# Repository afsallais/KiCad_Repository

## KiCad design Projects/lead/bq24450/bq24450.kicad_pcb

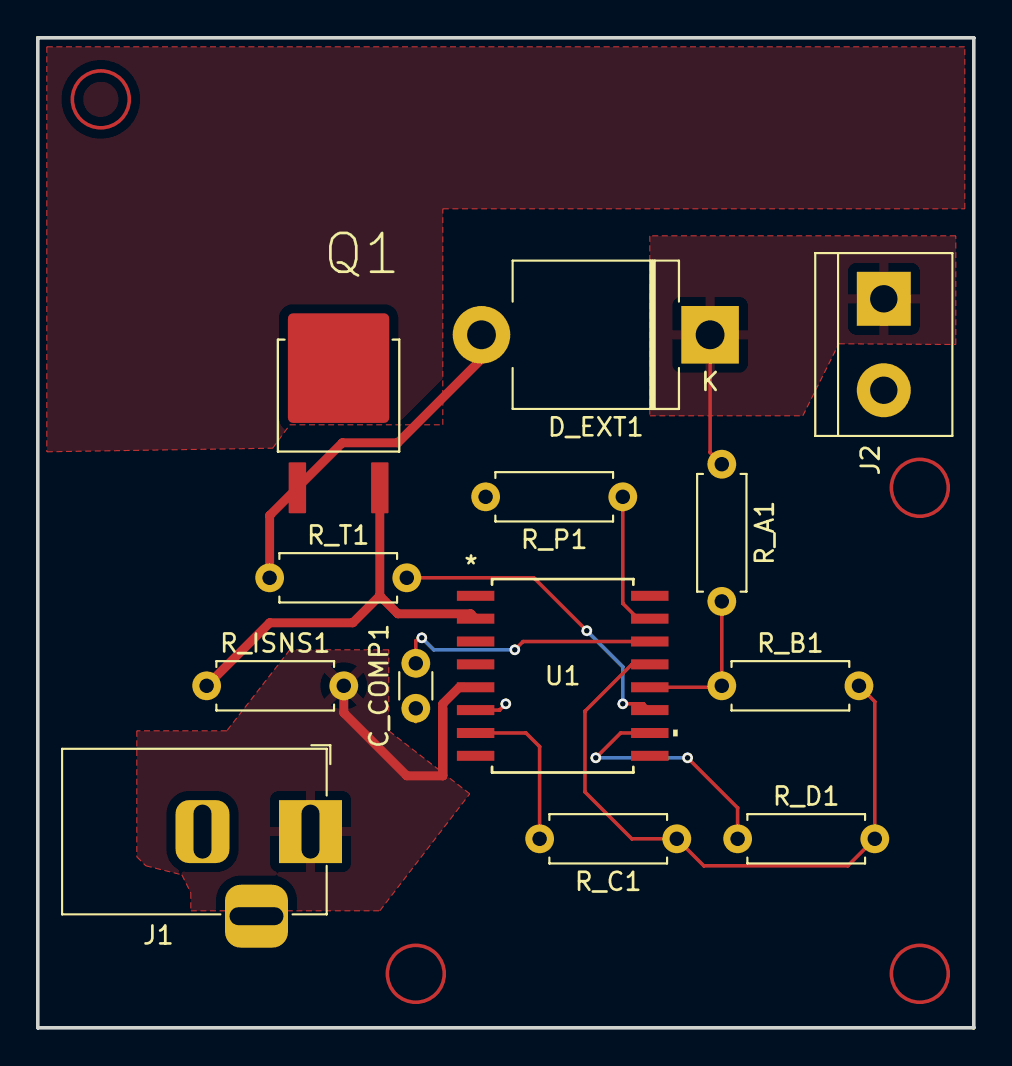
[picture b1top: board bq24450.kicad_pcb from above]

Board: 2 copper layers, 52.0 x 55.0 mm, 13 parts (0 on the bottom side), 13 nets.

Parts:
C_COMP1: C; C_Disc_D3.0mm_W1.6mm_P2.50mm
D_EXT1: D; D_5KPW_P12.70mm_Horizontal
J1: Jack-DC; BarrelJack_Horizontal
J2: Screw_Terminal_01x02; TerminalBlock_bornier-2_P5.08mm
Q1: PNP; MJD127T4GMJD127T4G
R_A1: R; R_Axial_DIN0207_L6.3mm_D2.5mm_P7.62mm_Horizontal
R_B1: R; R_Axial_DIN0207_L6.3mm_D2.5mm_P7.62mm_Horizontal
R_C1: R; R_Axial_DIN0207_L6.3mm_D2.5mm_P7.62mm_Horizontal
R_D1: R; R_Axial_DIN0207_L6.3mm_D2.5mm_P7.62mm_Horizontal
R_ISNS1: R; R_Axial_DIN0207_L6.3mm_D2.5mm_P7.62mm_Horizontal
R_P1: R; R_Axial_DIN0207_L6.3mm_D2.5mm_P7.62mm_Horizontal
R_T1: R; R_Axial_DIN0207_L6.3mm_D2.5mm_P7.62mm_Horizontal
U1: BQ24450DW

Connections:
CE: R_A1.2, R_B1.1, U1.12 (CE)
EXT_SUPPLY: J1.1, R_ISNS1.2, U1.3 (ISNSP), U1.5 (IN)
GND: C_COMP1.1, J1.2, J2.2, R_P1.2, U1.6 (GND)
ISNSM: Q1.3 (E), R_ISNS1.1, U1.2 (ISNSM), U1.4 (IFB)
unnamed: D_EXT1.2 (A), Q1.1 (C), R_T1.1
unnamed: C_COMP1.2, U1.14 (COMP)
unnamed: R_P1.1, U1.15 (DRVE)
PGOOD: R_C1.2, U1.7 (~PGOOD)
PRE_CHG: R_T1.2, U1.11 (PRE-CHG)
SHORT: U1.1 (ISNS), U1.8 (BSTOP)
SLA_BATTERY: D_EXT1.1 (K), J2.1, R_A1.1
STAT1: R_D1.1, U1.10 (STAT1)
VFB: R_B1.2, R_C1.1, R_D1.2, U1.13 (VFB)

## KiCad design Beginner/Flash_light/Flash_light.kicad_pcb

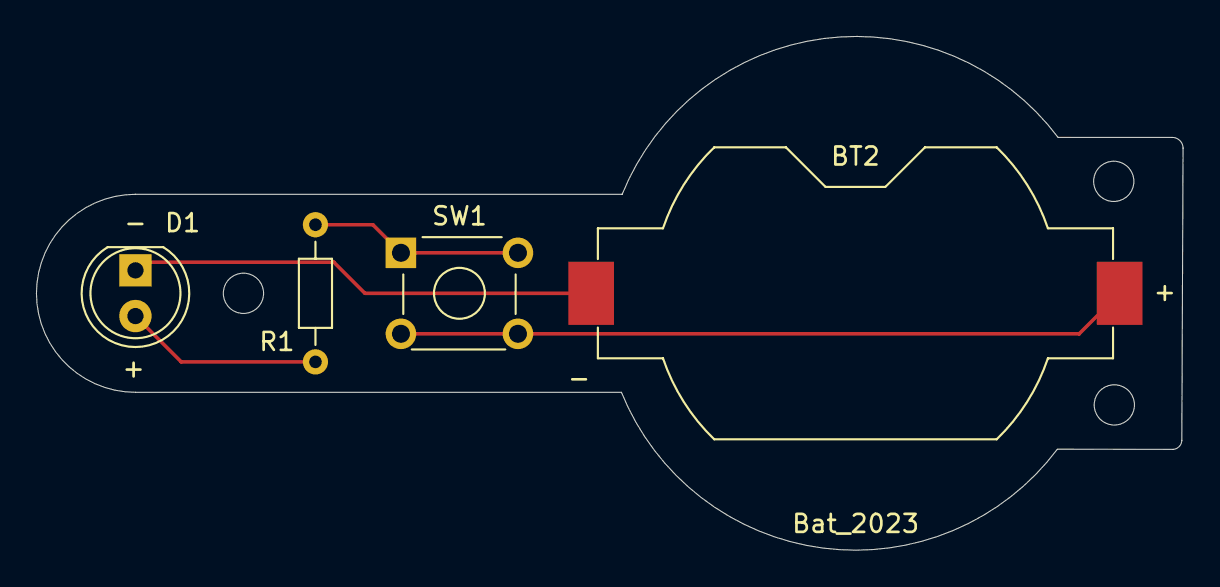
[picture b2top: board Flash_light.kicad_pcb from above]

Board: 2 copper layers, 63.7 x 28.5 mm, 4 parts (0 on the bottom side), 4 nets.

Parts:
BT2: Bat_2023; BatteryHolder_Keystone_1058_1x2032
D1: LED; LED_D5.0mm
R1: R; R_Axial_DIN0204_L3.6mm_D1.6mm_P7.62mm_Horizontal
SW1: SW_SPST; SW_TH_Tactile_Omron_B3F-10xx

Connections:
BAT_POS: BT2.1 (+), SW1.2 (B)
LED_A: D1.2 (A), R1.1
LED_K: BT2.2 (-), D1.1 (K)
unnamed: R1.2, SW1.1 (A)

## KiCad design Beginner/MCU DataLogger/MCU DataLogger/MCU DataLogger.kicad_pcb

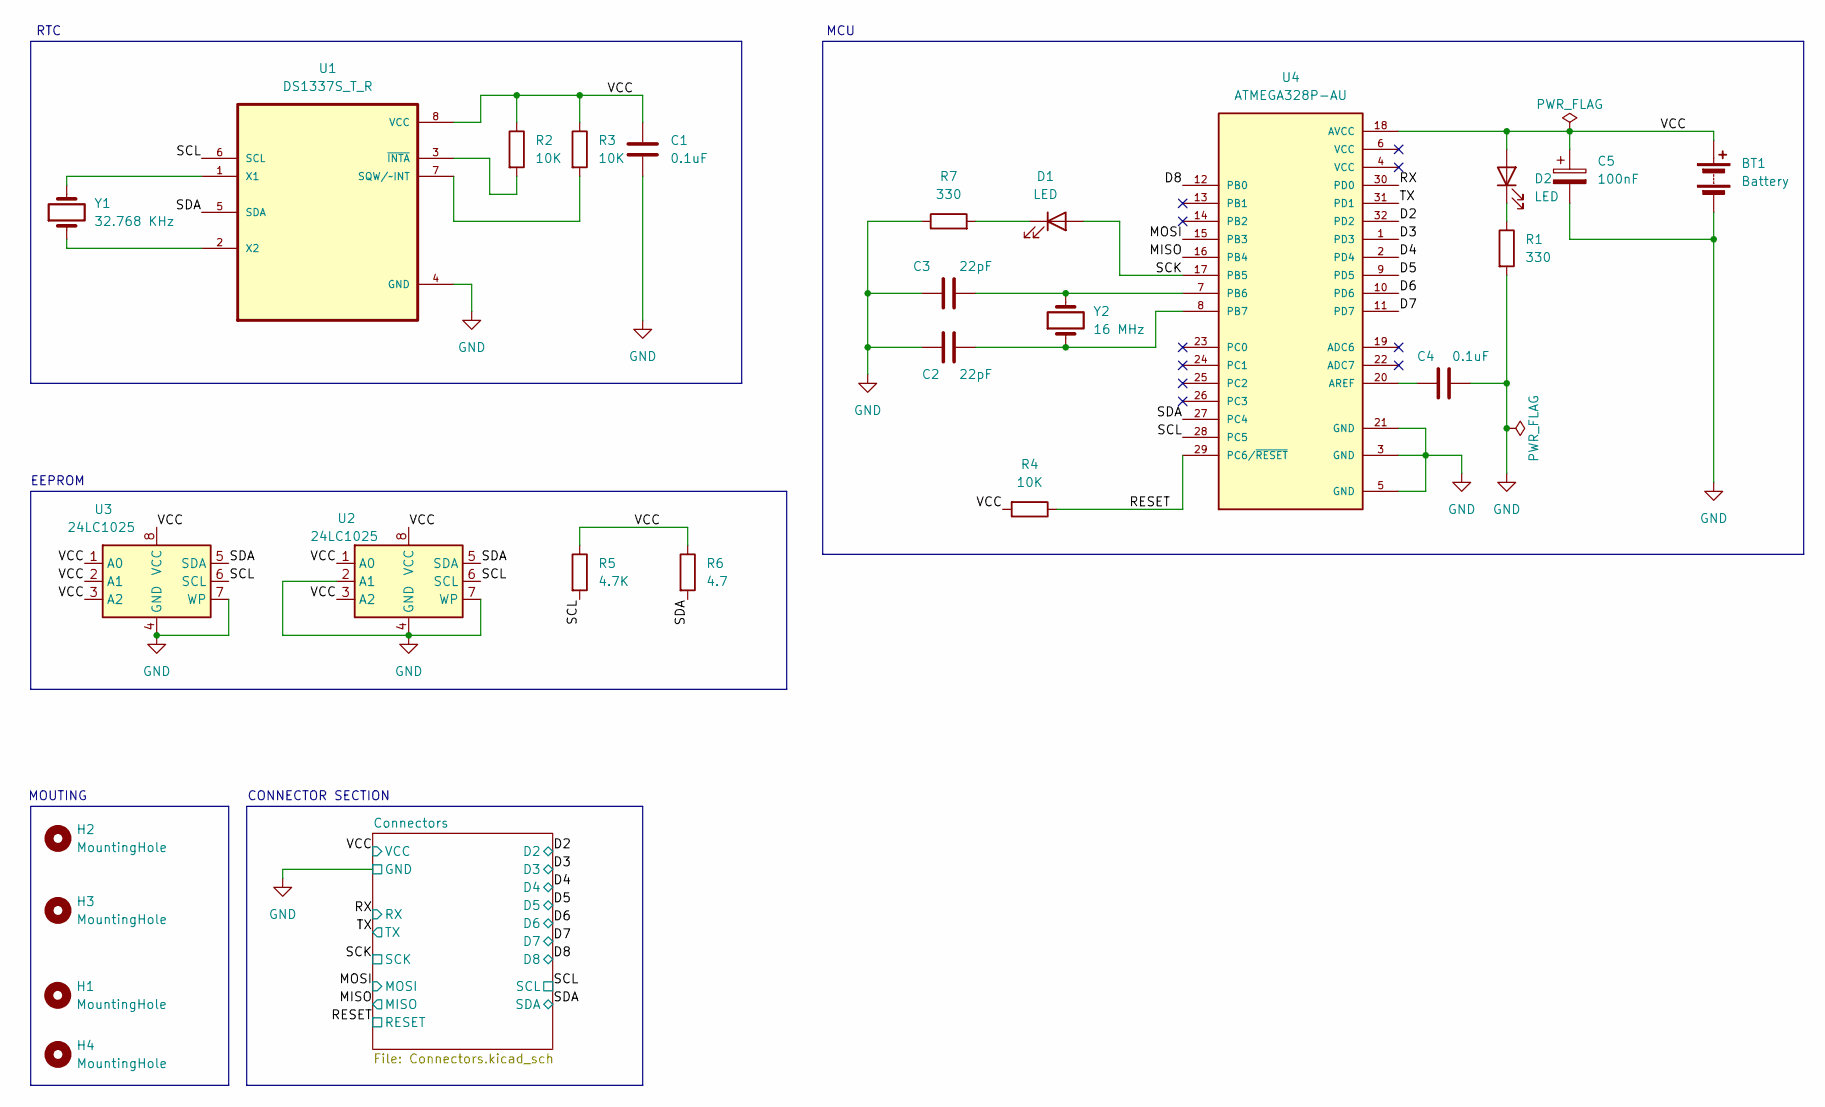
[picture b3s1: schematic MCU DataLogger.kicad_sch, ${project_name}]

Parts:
BT1: Battery; PinHeader_1x02_P2.54mm_Vertical
C1, C4: 0.1uF; C_0805_2012Metric
C2, C3: 22pF; C_0805_2012Metric
C5: 100nF; C_0805_2012Metric
D1, D2: LED; LED_0805_2012Metric
H1, H2, H3, H4: MountingHole; MountingHole_2.1mm
R1, R7: 330; R_0805_2012Metric
R2, R3, R4: 10K; R_0805_2012Metric
R5: 4.7K; R_0805_2012Metric
R6: 4.7; R_0805_2012Metric
U1: DS1337S_T_R; SOIC127P600X175-8N
U2, U3: 24LC1025; SOIC-8_5.23x5.23mm_P1.27mm
U4: ATMEGA328P-AU; QFP80P900X900X120-32N; PARTREV 8271A
Y1: 32.768 KHz; Crystal_SMD_5032-2Pin_5.0x3.2mm_HandSoldering
Y2: 16 MHz; Crystal_SMD_5032-2Pin_5.0x3.2mm_HandSoldering

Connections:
/D2: U4.32 (PD2); also elsewhere on the board
/D3: U4.1 (PD3); also elsewhere on the board
/D4: U4.2 (PD4); also elsewhere on the board
/D5: U4.9 (PD5); also elsewhere on the board
/D6: U4.10 (PD6); also elsewhere on the board
/D7: U4.11 (PD7); also elsewhere on the board
/D8: U4.12 (PB0); also elsewhere on the board
/MISO: U4.16 (PB4); also elsewhere on the board
/MOSI: U4.15 (PB3); also elsewhere on the board
/RESET: R4.1, U4.29 (PC6/~RESET); also elsewhere on the board
/RX: U4.30 (PD0); also elsewhere on the board
/SCK: D1.2 (A), U4.17 (PB5); also elsewhere on the board
/SCL: R5.2, U1.6 (SCL), U2.6 (SCL), U3.6 (SCL), U4.28 (PC5); also elsewhere on the board
/SDA: R6.2, U1.5 (SDA), U2.5 (SDA), U3.5 (SDA), U4.27 (PC4); also elsewhere on the board
/TX: U4.31 (PD1); also elsewhere on the board
/VCC: BT1.1 (+), C1.1, C5.1, D2.2 (A), R2.1, R3.1, R4.2, R5.1, R6.1, U1.8 (VCC), U2.1 (A0), U2.3 (A2), U2.8 (VCC), U3.1 (A0), U3.2 (A1), U3.3 (A2), U3.8 (VCC), U4.18 (AVCC); also elsewhere on the board
GND: BT1.2 (-), C1.2, C2.1, C3.2, C4.2, C5.2, R1.2, R7.1, U1.4 (GND), U2.2 (A1), U2.4 (GND), U2.7 (WP), U3.4 (GND), U3.7 (WP), U4.3 (GND), U4.5 (GND), U4.21 (GND); also elsewhere on the board
unnamed: D1.1 (K), R7.2
unnamed: D2.1 (K), R1.1
unnamed: R3.2, U1.7 (SQW/~INT)
unnamed: U1.1 (X1), Y1.2
unnamed: U1.2 (X2), Y1.1
unnamed: R2.2, U1.3 (~INTA)
unnamed: C4.1, U4.20 (AREF)
unnamed: C3.1, U4.7 (PB6), Y2.2
unnamed: C2.2, U4.8 (PB7), Y2.1

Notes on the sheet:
EEPROM
RTC
CONNECTOR SECTION
MOUTING
MCU

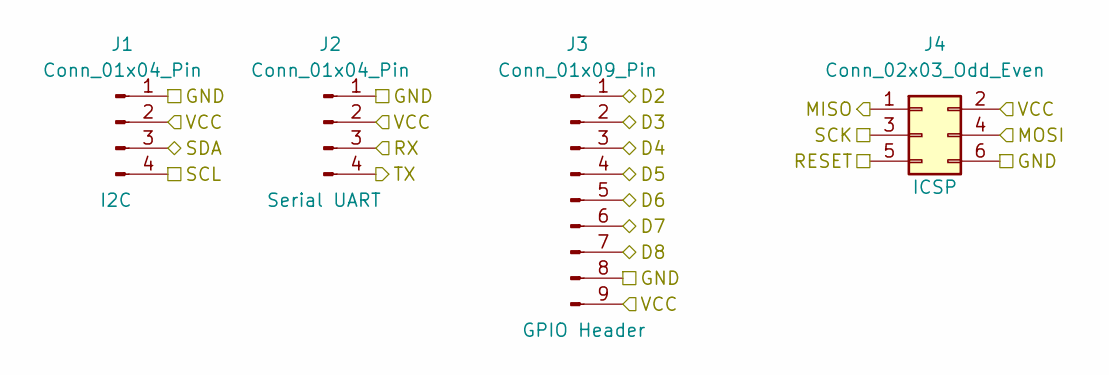
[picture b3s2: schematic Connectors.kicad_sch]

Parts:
J1, J2: Conn_01x04_Pin; PinHeader_1x04_P2.54mm_Vertical
J3: Conn_01x09_Pin; PinHeader_1x09_P2.54mm_Vertical
J4: Conn_02x03_Odd_Even; PinHeader_2x03_P2.54mm_Vertical

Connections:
/D2: J3.1; also elsewhere on the board
/D3: J3.2; also elsewhere on the board
/D4: J3.3; also elsewhere on the board
/D5: J3.4; also elsewhere on the board
/D6: J3.5; also elsewhere on the board
/D7: J3.6; also elsewhere on the board
/D8: J3.7; also elsewhere on the board
/MISO: J4.1; also elsewhere on the board
/MOSI: J4.4; also elsewhere on the board
/RESET: J4.5; also elsewhere on the board
/RX: J2.3; also elsewhere on the board
/SCK: J4.3; also elsewhere on the board
/SCL: J1.4; also elsewhere on the board
/SDA: J1.3; also elsewhere on the board
/TX: J2.4; also elsewhere on the board
/VCC: J1.2, J2.2, J3.9, J4.2; also elsewhere on the board
GND: J1.1, J2.1, J3.8, J4.6; also elsewhere on the board

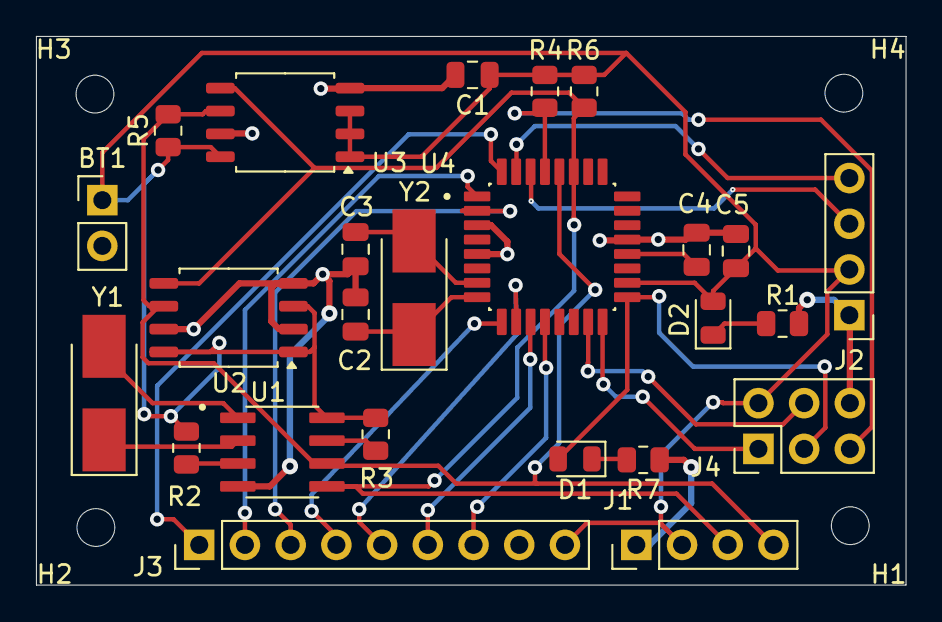
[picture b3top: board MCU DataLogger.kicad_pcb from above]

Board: 2 copper layers, 48.3 x 30.5 mm, 29 parts (0 on the bottom side), 26 nets.

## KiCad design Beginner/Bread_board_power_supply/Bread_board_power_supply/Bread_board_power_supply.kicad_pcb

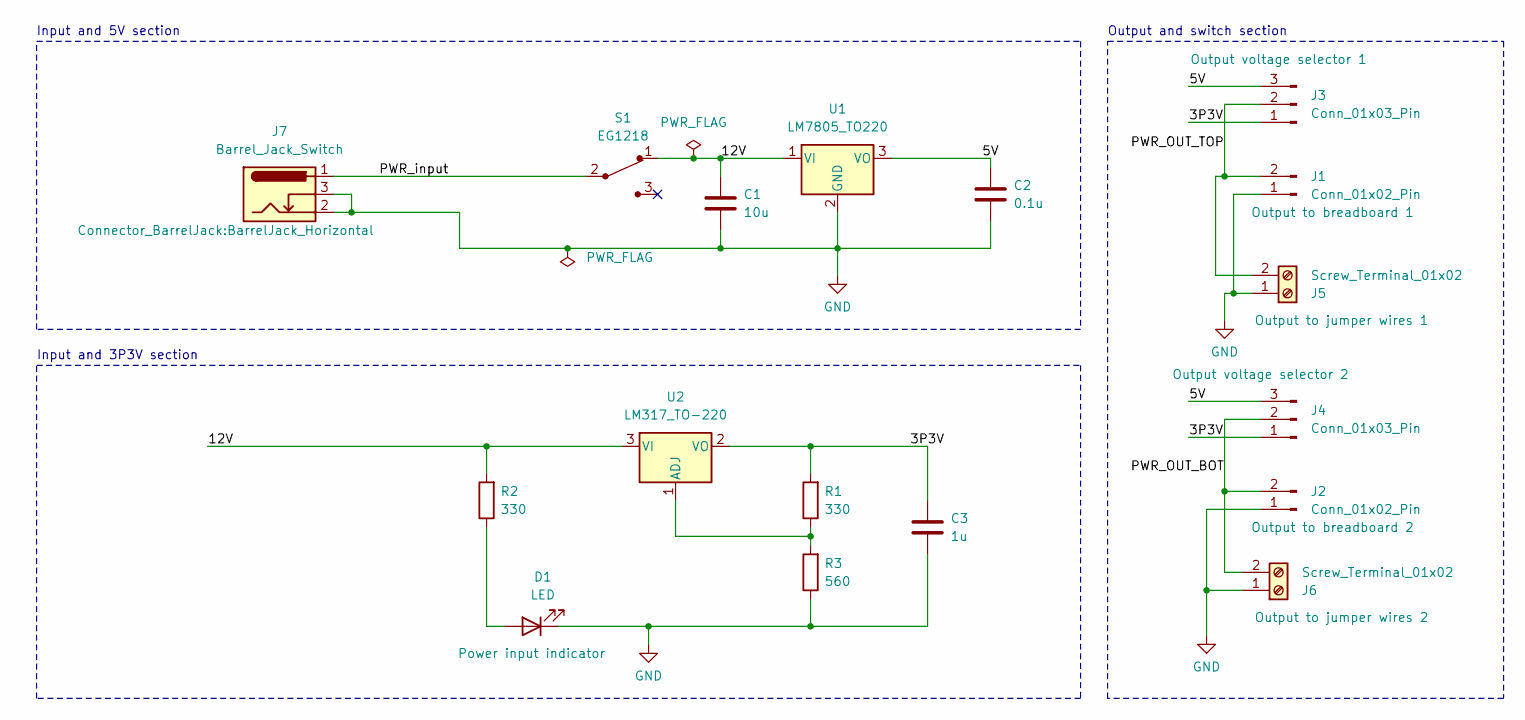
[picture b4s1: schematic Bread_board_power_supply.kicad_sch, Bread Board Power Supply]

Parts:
C1: 10u; C_Disc_D3.0mm_W1.6mm_P2.50mm
C2: 0.1u; C_Disc_D3.0mm_W1.6mm_P2.50mm
C3: 1u; C_Disc_D3.0mm_W1.6mm_P2.50mm
D1: LED; LED_D5.0mm
J1, J2: Conn_01x02_Pin; PinHeader_1x02_P2.54mm_Vertical
J3, J4: Conn_01x03_Pin; PinHeader_1x03_P2.54mm_Vertical
J5, J6: Screw_Terminal_01x02; TerminalBlock_bornier-2_P5.08mm
J7: Barrel_Jack_Switch; BarrelJack_Horizontal
R1, R2: 330; R_Axial_DIN0207_L6.3mm_D2.5mm_P7.62mm_Horizontal
R3: 560; R_Axial_DIN0207_L6.3mm_D2.5mm_P7.62mm_Horizontal
S1: EG1218; Switch_Slide_11.6x4mm_EG1218; MPN EG1218; Digi-Key_PN EG1903-ND
U1: LM7805_TO220; TO-220-3_Vertical
U2: LM317_TO-220; TO-220-3_Vertical

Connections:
/3P3V: C3.1, J3.1, J4.1, R1.2, U2.2 (VO)
/5V: C2.1, J3.3, J4.3, U1.3 (VO)
/12V: C1.1, R2.2, S1.1, U1.1 (VI), U2.3 (VI)
/PWR_OUT_BOT: J2.2, J4.2, J6.2
/PWR_OUT_TOP: J1.2, J3.2, J5.2
/PWR_input: J7.1, S1.2
GND: C1.2, C2.2, C3.2, D1.1 (K), J1.1, J2.1, J5.1, J6.1, J7.2, J7.3, R3.1, U1.2 (GND)
unnamed: D1.2 (A), R2.1
unnamed: R1.1, R3.2, U2.1 (ADJ)

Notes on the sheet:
Input and 3P3V section
Input and 5V section
Output and switch section

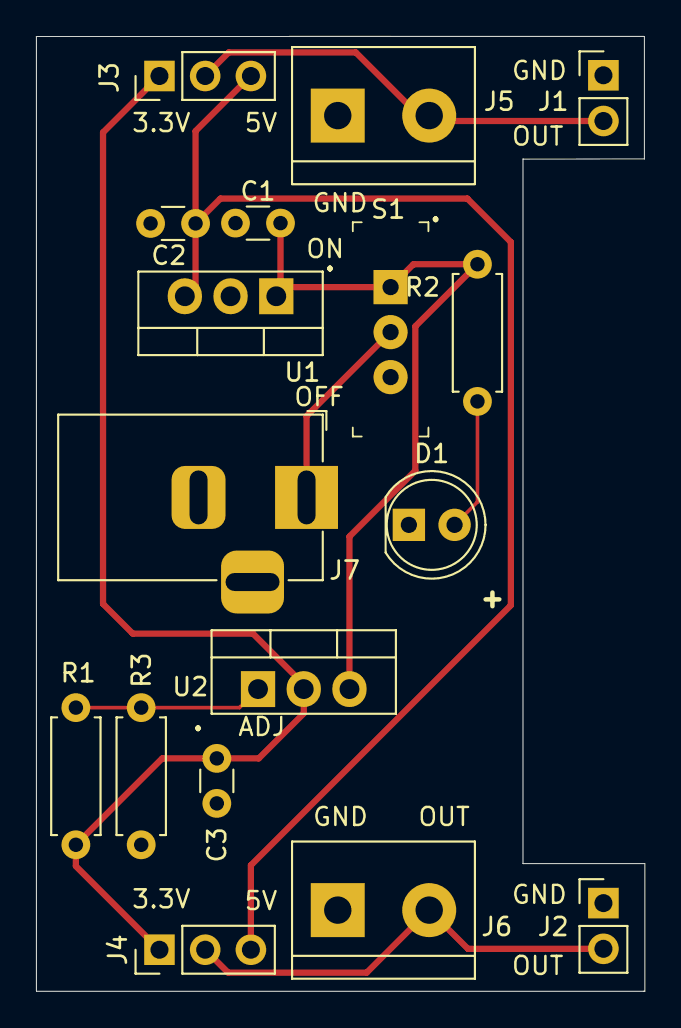
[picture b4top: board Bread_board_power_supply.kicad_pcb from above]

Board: 2 copper layers, 33.8 x 53.0 mm, 17 parts (0 on the bottom side), 9 nets.

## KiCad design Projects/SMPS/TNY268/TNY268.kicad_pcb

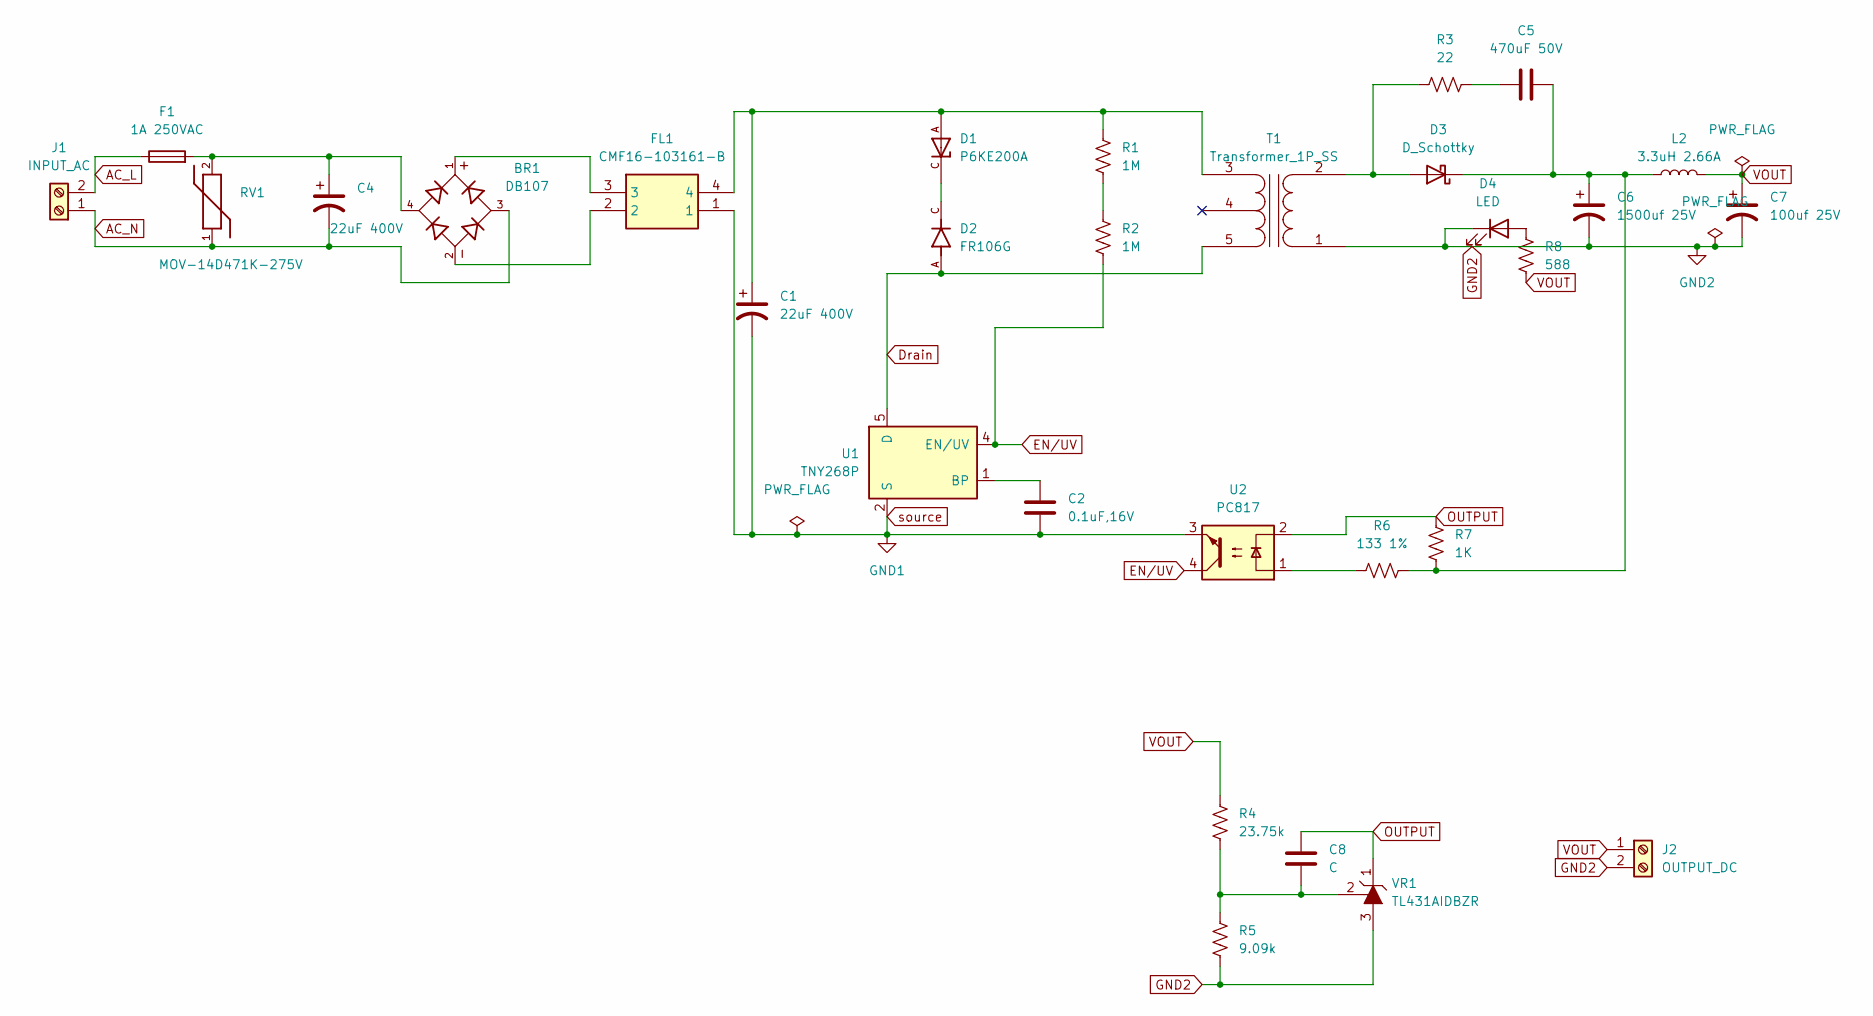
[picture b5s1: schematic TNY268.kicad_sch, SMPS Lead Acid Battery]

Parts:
BR1: DB107; DIP825W50P509L880H320Q4; PARTREV 13
C1, C4: 22uF 400V; CP_Radial_D10.0mm_P7.50mm
C2: 0.1uF,16V; CP_Radial_D7.5mm_P2.50mm
C5: 470uF 50V; CP_Radial_D7.5mm_P2.50mm
C6: 1500uf 25V; CP_Radial_D7.5mm_P2.50mm
C7: 100uf 25V; CP_Radial_D7.5mm_P2.50mm
C8: C; CP_Radial_D7.5mm_P2.50mm
D1: P6KE200A; DIOAD1276W78L760D360; PARTREV JC.10/26/20; DigiKey_Part_Number 2156-P6KE200A-ND
D2: FR106G; DIOAD1036W78L470D235; PARTREV P2104
D3: D_Schottky; D_3220_8050Metric_Pad2.65x5.15mm_HandSolder
D4: LED; LED_D5.0mm
F1: 1A 250VAC; Molex_KK-396_5273-02A_1x02_P3.96mm_Vertical
FL1: CMF16-103161-B; CMF16-103161; Mouser Part Number 553-CMF16-103161-B
J1: INPUT_AC; TerminalBlock_Altech_AK300-2_P5.00mm
J2: OUTPUT_DC; TerminalBlock_Altech_AK300-2_P5.00mm
L2: 3.3uH 2.66A; CD43 3.3uH 1A
R1, R2: 1M; R_Axial_DIN0207_L6.3mm_D2.5mm_P10.16mm_Horizontal
R3: 22; R_Axial_DIN0207_L6.3mm_D2.5mm_P10.16mm_Horizontal
R4: 23.75k; R_Axial_DIN0207_L6.3mm_D2.5mm_P10.16mm_Horizontal
R5: 9.09k; R_Axial_DIN0207_L6.3mm_D2.5mm_P10.16mm_Horizontal
R6: 133 1%; R_Axial_DIN0207_L6.3mm_D2.5mm_P10.16mm_Horizontal
R7: 1K; R_Axial_DIN0207_L6.3mm_D2.5mm_P10.16mm_Horizontal
R8: 588; R_Axial_DIN0207_L6.3mm_D2.5mm_P10.16mm_Horizontal
RV1: MOV-14D471K-275V; MOV14D471K; MOUSER_PART_NUMBER 652-MOV-14D471K
T1: Transformer_1P_SS; EE16-A2
U1: TNY268P; PowerIntegrations_PDIP-8B
U2: PC817; DIP-4_W7.62mm
VR1: TL431AIDBZR; SOT-23-3; MPN TL431AIDBZR; Digi-Key_PN 296-17329-1-ND

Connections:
AC_L: F1.1, J1.2
AC_N: BR1.3, C4.2, J1.1, RV1.1
EN/UV: R2.2, U1.4 (EN/UV), U2.4
GND1: C1.2, C2.2, FL1.1, U1.2 (S), U1.3 (S), U1.7 (S), U1.8 (S), U2.3
GND2: C6.2, C7.2, D4.1 (K), J2.2, R5.2, T1.1 (AA), VR1.3 (A)
unnamed: BR1.1, FL1.3
unnamed: BR1.2, FL1.2
unnamed: BR1.4, C4.1, F1.2, RV1.2
unnamed: C5.1, R3.2
unnamed: D1.C, D2.C
unnamed: D3.2 (A), R3.1, T1.2 (AB)
unnamed: C5.2, C6.1, D3.1 (K), L2.1, R6.2, R7.1
unnamed: D4.2 (A), R8.1
unnamed: R1.2, R2.1
unnamed: R6.1, U2.1
unnamed: C1.1, D1.A, FL1.4, R1.1, T1.3 (SA)
unnamed: D2.A, T1.5 (SB), U1.5 (D)
unnamed: C2.1, U1.1 (BP)
unnamed: C8.2, R4.2, R5.1, VR1.2 (REF)
OUTPUT: C8.1, R7.2, U2.2, VR1.1 (K)
VOUT: C7.1, J2.1, L2.2, R4.1, R8.2

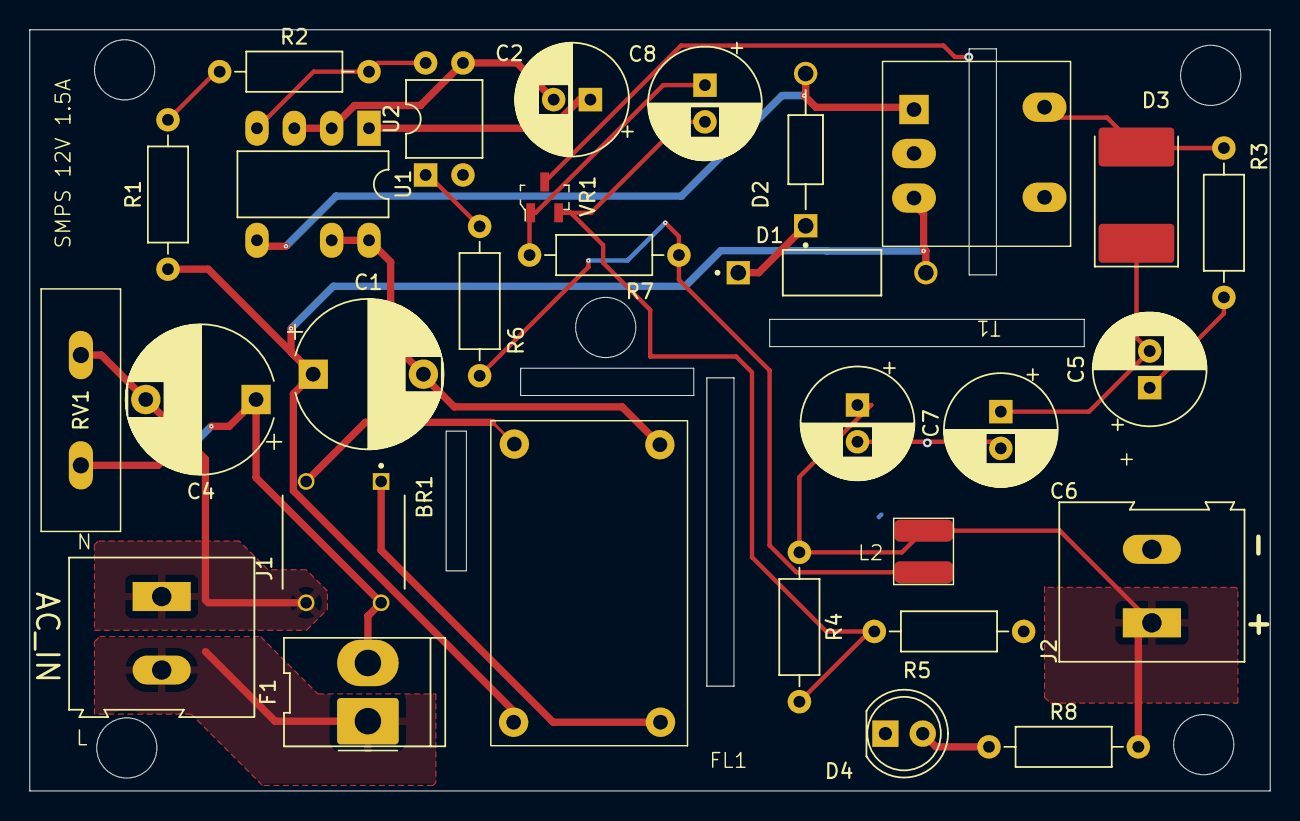
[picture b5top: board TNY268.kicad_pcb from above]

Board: 2 copper layers, 84.4 x 51.8 mm, 30 parts (0 on the bottom side), 21 nets.

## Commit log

2025-09-16 projects
2025-09-16 beginner
2025-09-28 new things for charger
2025-10-01 added routing
